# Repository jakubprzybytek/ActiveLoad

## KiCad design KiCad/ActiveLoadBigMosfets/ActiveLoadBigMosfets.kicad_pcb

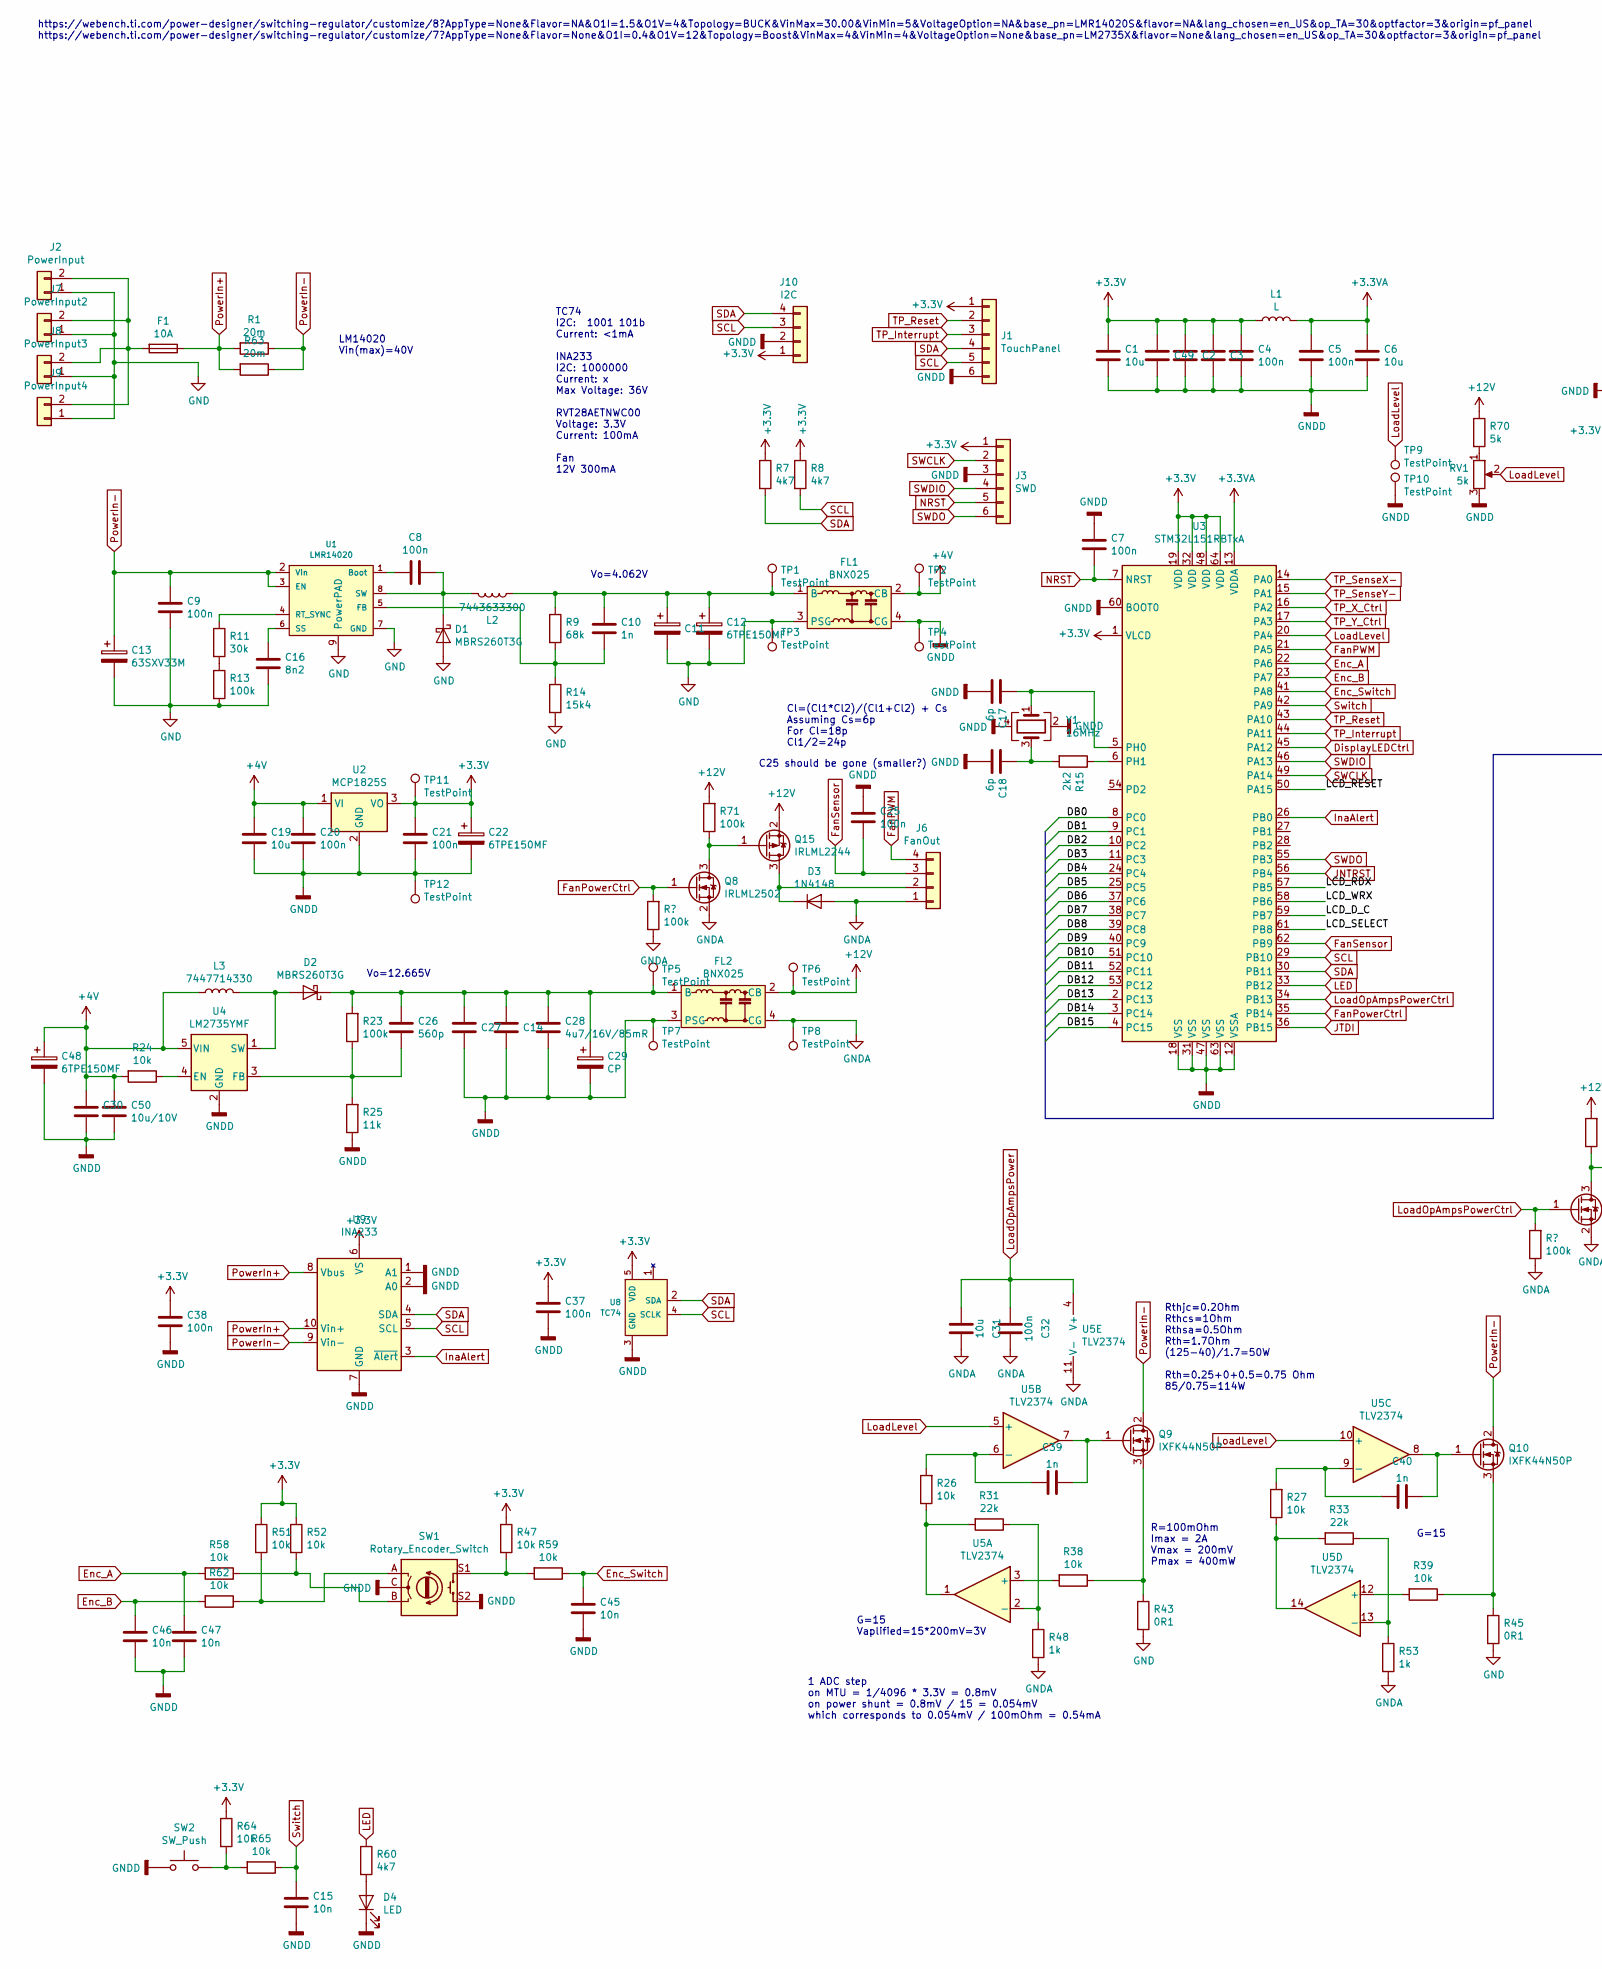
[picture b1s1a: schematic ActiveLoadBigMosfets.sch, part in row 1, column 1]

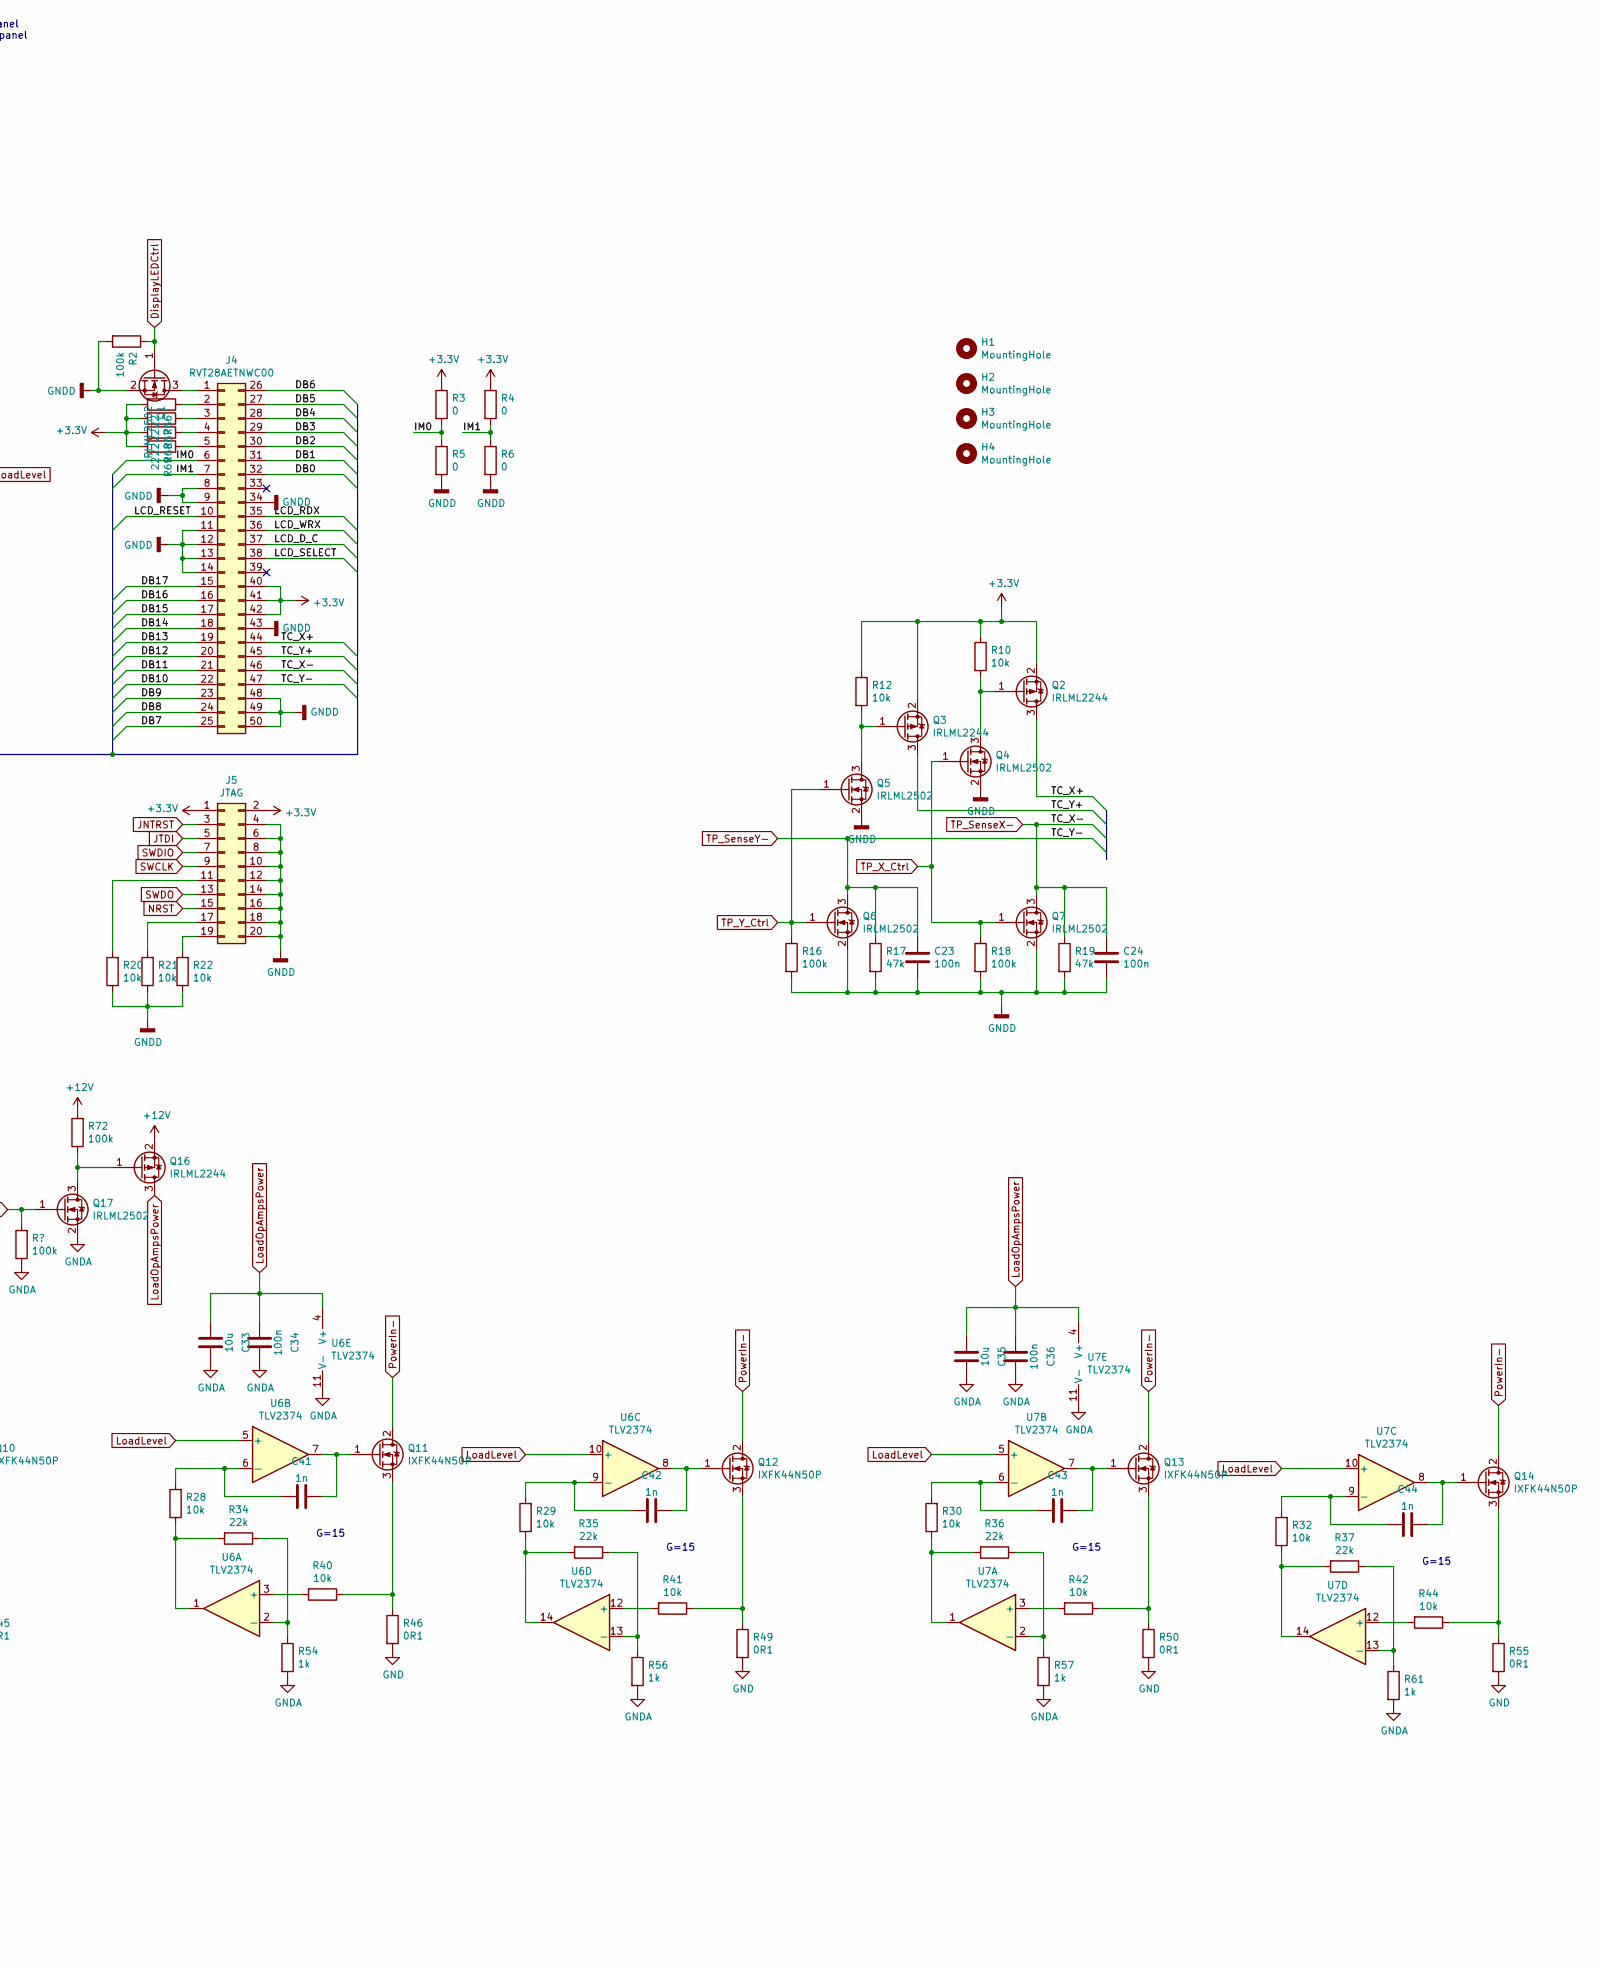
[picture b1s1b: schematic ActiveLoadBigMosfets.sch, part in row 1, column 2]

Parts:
C1, C6, C19, C31, C33, C35: 10u; C_0805_2012Metric
C2, C3, C4, C5, C7, C8, C9, C20, C21, C23, C24, C25, C32, C34, C36, C37, C38, C49: 100n; C_0603_1608Metric
C10, C39, C40, C41, C42, C43, C44: 1n; C_0805_2012Metric
C11, C12, C22, C48: 6TPE150MF; CP_EIA-7343-31_Kemet-D
C13: 63SXV33M; CP_Elec_8x11.9
C14, C27, C28: 4u7/16V/85mR; C_0805_2012Metric
C15, C45, C46, C47: 10n; C_0805_2012Metric
C16: 8n2; C_0805_2012Metric
C17, C18: 6p; C_0805_2012Metric
C26: 560p; C_0805_2012Metric
C29: CP; CP_Elec_6.3x7.7
C30, C50: 10u/10V; C_0805_2012Metric
D1, D2: MBRS260T3G; D_SMB
D3: 1N4148; D_MiniMELF
D4: LED; LED_0805_2012Metric
F1: 10A; Fuseholder5x20_horiz_open_inline_Type-I
FL1, FL2: BNX025; Filter_Murata_BNX025
H1, H2, H3, H4: MountingHole; MountingHole_3.2mm_M3
J1: TouchPanel; TE_0-1734839-6_1x06-1MP_P0.5mm_Horizontal
J2: PowerInput; SolderingHoles-2_P6.00mm_D2.0mm
J3: SWD; PinHeader_1x06_P2.54mm_Vertical
J4: RVT28AETNWC00; Molex-50S-0.5SH_1x50-P0.50mm_Horizontal
J5: JTAG; PinHeader_2x10_P2.54mm_Vertical_SMD
J6: FanOut; FanPinHeader_1x04_P2.54mm_Vertical
J7: PowerInput2; SolderingHoles-2_P6.00mm_D2.0mm
J8: PowerInput3; SolderingHoles-2_P6.00mm_D2.0mm
J9: PowerInput4; SolderingHoles-2_P6.00mm_D2.0mm
J10: I2C; PinHeader_1x04_P2.54mm_Vertical
L1: L; L_0805_2012Metric
L2: 7443633300; L_Wuerth_WE-HCF
L3: 7447714330; L_Wuerth_WE-PDF_Handsoldering
Q1, Q4, Q5, Q6, Q7, Q8, Q17: IRLML2502; SOT-23
Q2, Q3, Q15, Q16: IRLML2244; SOT-23
Q9, Q10, Q11, Q12, Q13, Q14: IXFK44N50P; TO-264-3_Vertical
R1, R63: 20m; R_2512_6332Metric_Pad1.52x3.35mm_HandSolder
R2, R13, R16, R18, R23, R71, R72: 100k; R_0805_2012Metric
R3, R6: 0; SolderJumper-2_P1.3mm_Bridged_RoundedPad1.0x1.5mm
R4, R5: 0; SolderJumper-2_P1.3mm_Open_RoundedPad1.0x1.5mm
R7, R8, R60: 4k7; R_0805_2012Metric
R9: 68k; R_0805_2012Metric
R10, R12, R20, R21, R22, R24, R26, R27, R28, R29, R30, R32, R38, R39, R40, R41, R42, R44, R47, R51, R52, R58, R59, R62, R64, R65: 10k; R_0603_1608Metric
R11: 30k; R_0805_2012Metric
R14: 15k4; R_0805_2012Metric
R15: 2k2; R_0805_2012Metric
R17, R19: 47k; R_0805_2012Metric
R25: 11k; R_0805_2012Metric
R31, R33, R34, R35, R36, R37: 22k; R_0805_2012Metric
R43, R45, R46, R49, R50, R55: 0R1; R_2512_6332Metric_Pad1.52x3.35mm_HandSolder
R48, R53, R54, R56, R57, R61: 1k; R_0805_2012Metric
R66, R67, R68, R69: 22; R_0805_2012Metric
R70: 5k; R_0805_2012Metric
RV1: 5k; Potentiometer_ACP_CA6-VSMD_Vertical
SW1: Rotary_Encoder_Switch; RotaryEncoder_Alps_EC11E-Switch_Vertical_H20mm_CircularMoun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
SW2: SW_Push; SW_SPST_B3S-1000
TP1, TP2, TP3, TP4, TP5, TP6, TP7, TP8, TP9, TP10, TP11, TP12: TestPoint; TestPoint_THTPad_1.5x1.5mm_Drill0.7mm
U1: LMR14020; SOIC-8-1EP_3.9x4.9mm_P1.27mm_EP2.41x3.3mm_ThermalVias
U2: MCP1825S; SOT-223-3_TabPin2
U3: STM32L151RBTxA; LQFP-64_10x10mm_P0.5mm
U4: LM2735YMF; SOT-23-5_HandSoldering
U5, U6, U7: TLV2374; SOIC-14_3.9x8.7mm_P1.27mm
U8: TC74; PinHeader_1x05_P2.54mm_Vertical
U9: INA233; VSSOP-10_3x3mm_P0.5mm
Y1: 16MHz; Crystal_SMD_Abracon_ABM3B-4Pin_5.0x3.2mm

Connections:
+3.3VA: C5.1, C6.1, L1.2, U3.13 (VDDA)
+3V3: C1.1, C2.1, C3.1, C4.1, C21.1, C22.1, C37.1, C38.1, C49.1, J1.1, J3.1, J4.40, J4.41, J4.42, J5.1, J5.2, J10.1, L1.1, Q2.2 (S), Q3.2 (S), R3.1, R4.1, R7.1, R8.1, R10.1, R12.1, R47.1, R51.1, R52.1, R64.1, R66.2, R67.2, R68.2, R69.2, TP11.1, U2.3 (VO), U3.1 (VLCD), U3.19 (VDD), U3.32 (VDD), U3.48 (VDD), U3.64 (VDD), U8.5 (VDD), U9.6 (VS)
+4V: C19.1, C20.1, C30.1, C48.1, C50.1, FL1.2 (CB), L3.1, R24.2, TP2.1, U2.1 (VI), U4.5 (VIN)
+12V: FL2.2 (CB), Q15.2 (S), Q16.2 (S), R70.1, R71.2, R72.2, TP6.1
/DB0: J4.32, U3.8 (PC0)
/DB1: J4.31, U3.9 (PC1)
/DB2: J4.30, U3.10 (PC2)
/DB3: J4.29, U3.11 (PC3)
/DB4: J4.28, U3.24 (PC4)
/DB5: J4.27, U3.25 (PC5)
/DB6: J4.26, U3.37 (PC6)
/DB7: J4.25, U3.38 (PC7)
/DB8: J4.24, U3.39 (PC8)
/DB9: J4.23, U3.40 (PC9)
/DB10: J4.22, U3.51 (PC10)
/DB11: J4.21, U3.52 (PC11)
/DB12: J4.20, U3.53 (PC12)
/DB13: J4.19, U3.2 (PC13)
/DB14: J4.18, U3.3 (PC14)
/DB15: J4.17, U3.4 (PC15)
/DB16: J4.16
/DB17: J4.15
/IM0: J4.6, R3.2, R5.1
/IM1: J4.7, R4.2, R6.1
/LCD_D_C: J4.37, U3.59 (PB7)
/LCD_RDX: J4.35, U3.57 (PB5)
/LCD_RESET: J4.10, U3.50 (PA15)
/LCD_SELECT: J4.38, U3.61 (PB8)
/LCD_WRX: J4.36, U3.58 (PB6)
/TC_X+: J4.44, Q2.3 (D)
/TC_Y+: J4.45, Q3.3 (D)
DisplayLEDCtrl: Q1.1 (G), R2.1, U3.45 (PA12)
Enc_A: C47.1, R58.2, U3.22 (PA6)
Enc_B: C46.1, R62.2, U3.23 (PA7)
Enc_Switch: C45.1, R59.1, U3.41 (PA8)
FanPWM: J6.4, U3.21 (PA5)
FanPowerCtrl: Q8.1 (G), U3.35 (PB14)
FanSensor: C25.2, J6.3, U3.62 (PB9)
GND: C9.2, C11.2, C12.2, C13.2, C16.2, D1.2 (A), FL1.3 (PSG), J2.1, J7.1, J8.1, J9.1, R13.2, R14.2, R43.2, R45.2, R46.2, R49.2, R50.2, R55.2, TP3.1, U1.7 (GND), U1.9 (PowerPAD)
GNDA: C31.2, C32.2, C33.1, C34.2, C35.2, C36.2, D3.2 (A), FL2.4 (CG), J6.1, Q8.2 (S), Q17.2 (S), R48.2, R53.2, R54.2, R56.2, R57.2, R61.2, TP8.1, U5.11 (V-), U6.11 (V-), U7.11 (V-)
GNDD: C1.2, C2.2, C3.2, C4.2, C5.2, C6.2, C7.1, C14.2, C15.2, C17.2, C18.2, C19.2, C20.2, C21.2, C22.2, C23.2, C24.2, C25.1, C27.2, C28.2, C29.2, C30.2, C37.2, C38.2, C45.2, C46.2, C47.2, C48.2, C49.2, C50.2, D4.1 (K), FL1.4 (CG), FL2.3 (PSG), J1.6, J3.3, J4.8, J4.9, J4.11, J4.12, J4.13, J4.14, J4.34, J4.43, J4.48, J4.49, J4.50, J5.4, J5.6, J5.8, J5.10, J5.12, J5.14, J5.16, J5.18, J5.20, J10.2, Q1.2 (S), Q4.2 (S), Q5.2 (S), Q6.2 (S), Q7.2 (S), R2.2, R5.2, R6.2, R16.2, R17.2, R18.2, R19.2, R20.1, R21.1, R22.1, R25.1, RV1.3, SW1.C, SW1.S2, SW2.1, TP4.1, TP7.1, TP10.1, TP12.1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
InaAlert: U3.26 (PB0), U9.3 (~Alert~)
JNTRST: J5.3, U3.56 (PB4)
JTDI: J5.5, U3.36 (PB15)
LED: R60.1, U3.33 (PB12)
LoadLevel: RV1.2, TP9.1, U3.20 (PA4), U5.5 (+), U5.10 (+), U6.5 (+), U6.10 (+), U7.5 (+), U7.10 (+)
LoadOpAmpsPower: C31.1, C32.1, C33.2, C34.1, C35.1, C36.1, Q16.3 (D), U5.4 (V+), U6.4 (V+), U7.4 (V+)
LoadOpAmpsPowerCtrl: Q17.1 (G), U3.34 (PB13)
NRST: C7.2, J3.5, J5.15, U3.7 (NRST)
unnamed: C8.1, D1.1 (K), L2.2, U1.8 (SW)
unnamed: C8.2, U1.1 (Boot)
unnamed: C10.1, C11.1, C12.1, FL1.1 (B), L2.1, R9.1, TP1.1
unnamed: C10.2, R9.2, R14.1, U1.5 (FB)
unnamed: C14.1, C26.1, C27.1, C28.1, C29.1, D2.1 (K), FL2.1 (B), R23.2, TP5.1
unnamed: C16.1, U1.6 (SS)
unnamed: C17.1, U3.5 (PH0), Y1.1
unnamed: C18.1, R15.2, Y1.3
unnamed: C26.2, R23.1, R25.2, U4.3 (FB)
unnamed: C39.1, R26.2, U5.6 (-)
unnamed: C39.2, Q9.1 (G), U5.7
unnamed: C40.1, R27.2, U5.9 (-)
unnamed: C40.2, Q10.1 (G), U5.8
unnamed: C41.1, R28.2, U6.6 (-)
unnamed: C41.2, Q11.1 (G), U6.7
unnamed: C42.1, R29.2, U6.9 (-)
unnamed: C42.2, Q12.1 (G), U6.8
unnamed: C43.1, R30.2, U7.6 (-)
unnamed: C43.2, Q13.1 (G), U7.7
unnamed: C44.1, R32.2, U7.9 (-)
unnamed: C44.2, Q14.1 (G), U7.8
unnamed: D2.2 (A), L3.2, U4.1 (SW)
unnamed: D3.1 (K), J6.2, Q15.3 (D)
unnamed: D4.2 (A), R60.2
unnamed: F1.2, J2.2, J7.2, J8.2, J9.2
unnamed: J4.1, Q1.3 (D)
unnamed: J4.2, R66.1
unnamed: J4.3, R67.1
unnamed: J4.4, R68.1
unnamed: J4.5, R69.1
unnamed: J5.11, R20.2
unnamed: J5.17, R21.2
unnamed: J5.19, R22.2
unnamed: Q2.1 (G), Q4.3 (D), R10.2
unnamed: Q3.1 (G), Q5.3 (D), R12.2
unnamed: Q9.3 (S), R38.1, R43.1
unnamed: Q10.3 (S), R39.1, R45.1
unnamed: Q11.3 (S), R40.1, R46.1
unnamed: Q12.3 (S), R41.1, R49.1
unnamed: Q13.3 (S), R42.1, R50.1
unnamed: Q14.3 (S), R44.1, R55.1
unnamed: Q8.3 (D), Q15.1 (G), R71.1
unnamed: Q16.1 (G), Q17.3 (D), R72.1
unnamed: R11.1, U1.4 (RT_SYNC)
unnamed: R11.2, R13.1
unnamed: R15.1, U3.6 (PH1)
unnamed: R24.1, U4.4 (EN)
unnamed: R26.1, R31.2, U5.1
unnamed: R27.1, R33.2, U5.14
unnamed: R28.1, R34.2, U6.1
unnamed: R29.1, R35.2, U6.14
unnamed: R30.1, R36.2, U7.1
unnamed: R31.1, R48.1, U5.2 (-)
unnamed: R32.1, R37.2, U7.14
unnamed: R33.1, R53.1, U5.13 (-)
unnamed: R34.1, R54.1, U6.2 (-)
unnamed: R35.1, R56.1, U6.13 (-)
unnamed: R36.1, R57.1, U7.2 (-)
unnamed: R37.1, R61.1, U7.13 (-)
unnamed: R38.2, U5.3 (+)
unnamed: R39.2, U5.12 (+)
unnamed: R40.2, U6.3 (+)
unnamed: R41.2, U6.12 (+)
unnamed: R42.2, U7.3 (+)
unnamed: R44.2, U7.12 (+)
unnamed: R47.2, R59.2, SW1.S1
unnamed: R51.2, R62.1, SW1.A
unnamed: R52.2, R58.1, SW1.B
unnamed: R64.2, R65.2, SW2.2
unnamed: R70.2, RV1.1
PowerIn+: F1.1, R1.2, R63.2, U9.8 (Vbus), U9.10 (Vin+)
PowerIn-: C9.1, C13.1, Q9.2 (D), Q10.2 (D), Q11.2 (D), Q12.2 (D), Q13.2 (D), Q14.2 (D), R1.1, R63.1, U1.2 (Vin), U1.3 (EN), U9.9 (Vin-)
SCL: J1.5, J10.3, R8.2, U3.29 (PB10), U8.4 (SCLK), U9.5 (SCL)
SDA: J1.4, J10.4, R7.2, U3.30 (PB11), U8.2 (SDA), U9.4 (SDA)
SWCLK: J3.2, J5.9, U3.49 (PA14)
SWDIO: J3.4, J5.7, U3.46 (PA13)
SWDO: J3.6, J5.13, U3.55 (PB3)
Switch: C15.1, R65.1, U3.42 (PA9)
TP_Interrupt: J1.3, U3.44 (PA11)
TP_Reset: J1.2, U3.43 (PA10)
TP_SenseX-: C24.1, J4.46, Q7.3 (D), R19.1, U3.14 (PA0)
TP_SenseY-: C23.1, J4.47, Q6.3 (D), R17.1, U3.15 (PA1)
TP_X_Ctrl: Q4.1 (G), Q7.1 (G), R18.1, U3.16 (PA2)
TP_Y_Ctrl: Q5.1 (G), Q6.1 (G), R16.1, U3.17 (PA3)

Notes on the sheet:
LM14020 Vin(max)=40V
TC74 I2C: 1001 101b Current: <1mA INA233 I2C: 1000000 Current: x Max Voltage: 36V RVT28AETNWC00 Voltage: 3.3V Current: 100mA Fan 12V 300mA
https://webench.ti.com/power-designer/switching-regulator/customize/8?AppType=None&Flavor=NA&O1I=1.5&O1V=4&Topology=BUCK&VinMax=30.00&VinMin=5&VoltageOption=NA&base_pn=LMR14020S&flavor=NA&lang_chosen=en_US&op_TA=30&optfactor=3&origin=pf_panel https://webench.ti.com/power-designer/switching-regulato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
R=100mOhm Imax = 2A Vmax = 200mV Pmax = 400mW
Rthjc=0.2Ohm Rthcs=1Ohm Rthsa=0.5Ohm Rth=1.7Ohm (125-40)/1.7=50W Rth=0.25+0+0.5=0.75 Ohm 85/0.75=114W
G=15 Vaplified=15*200mV=3V
G=15
Vo=4.062V
Vo=12.665V
1 ADC step on MTU = 1/4096 * 3.3V = 0.8mV on power shunt = 0.8mV / 15 = 0.054mV which corresponds to 0.054mV / 100mOhm = 0.54mA
Cl=(Cl1*Cl2)/(Cl1+Cl2) + Cs Assuming Cs=6p For Cl=18p Cl1/2=24p
C25 should be gone (smaller?)

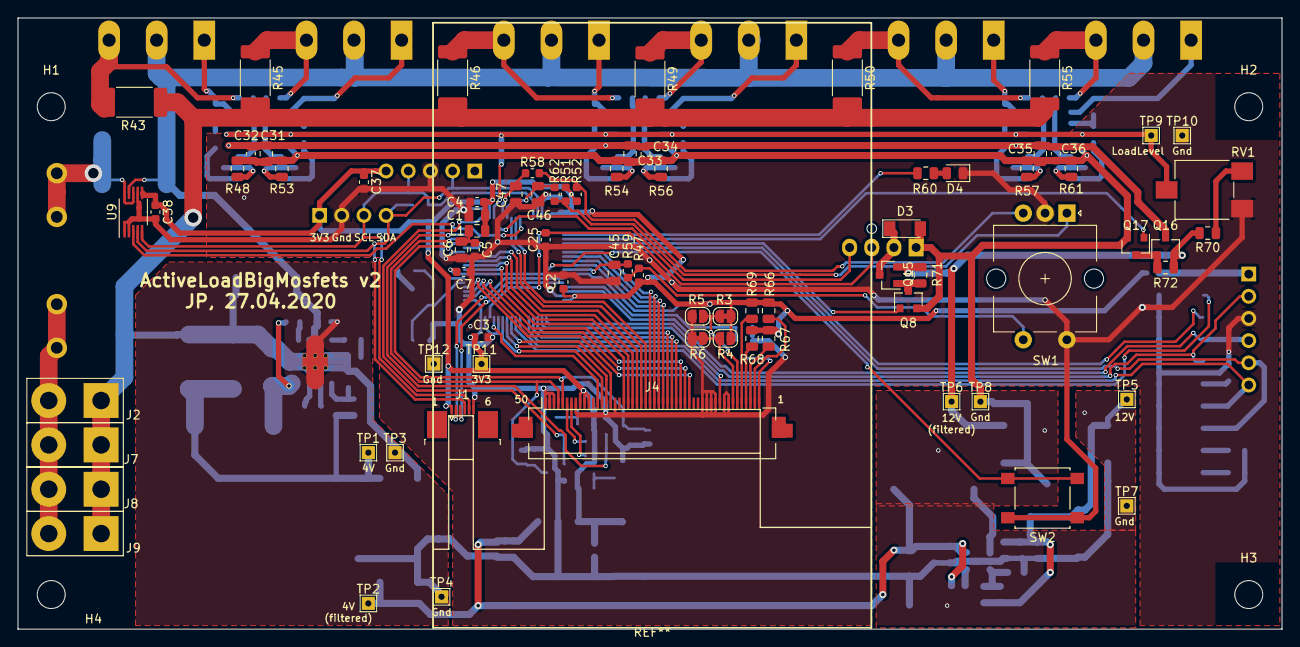
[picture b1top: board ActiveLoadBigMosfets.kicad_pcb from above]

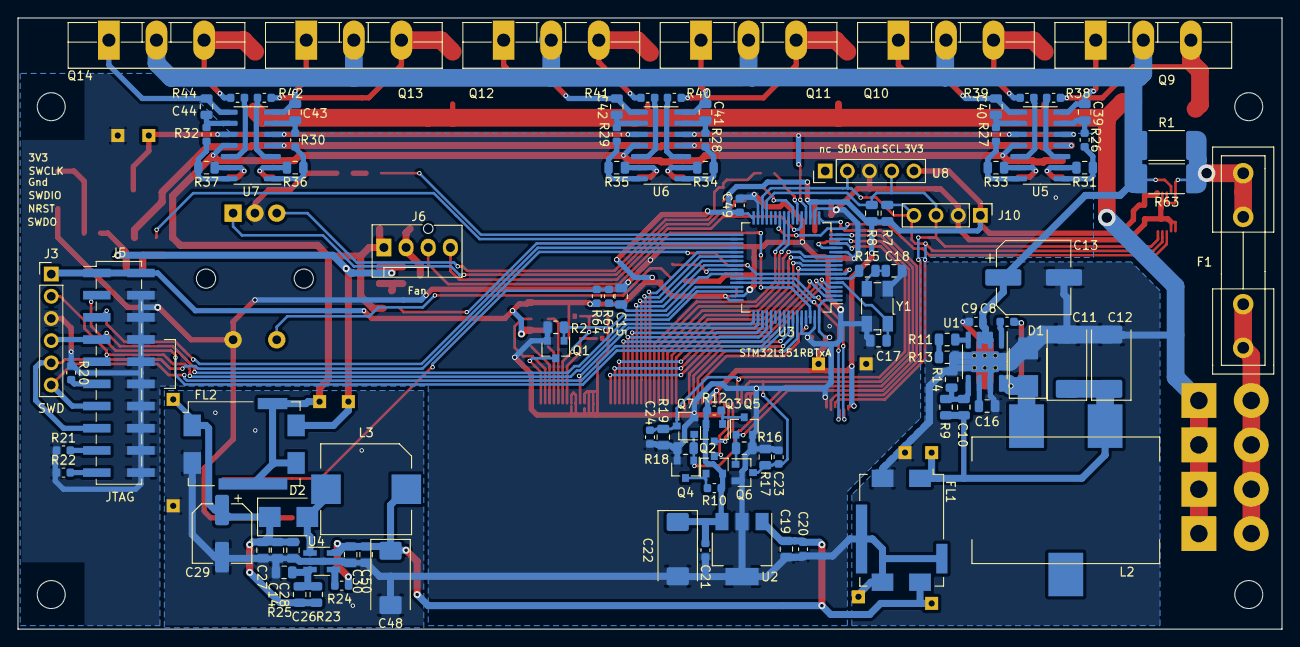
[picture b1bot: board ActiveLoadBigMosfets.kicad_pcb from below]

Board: 2 copper layers, 144.8 x 70.0 mm, 188 parts (106 on the bottom side), 131 nets.

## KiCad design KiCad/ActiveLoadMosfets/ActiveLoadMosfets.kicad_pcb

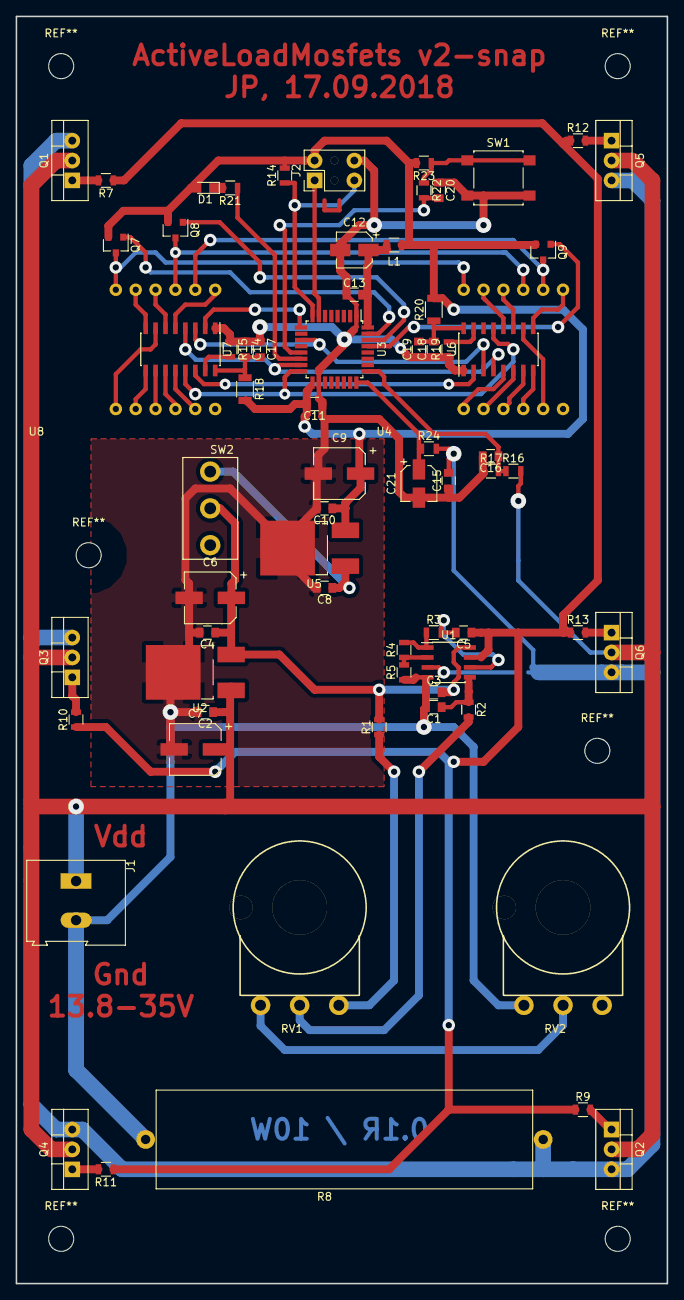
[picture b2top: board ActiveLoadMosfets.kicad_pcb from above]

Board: 2 copper layers, 83.2 x 161.9 mm, 70 parts (1 on the bottom side), 61 nets.

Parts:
C1: 220n; C_0805
C2: 470n; C_0805
C3, C4, C8, C10, C11, C13, C15, C16: 100n; C_0805
C5: 1n; C_0805
C6, C7, C9: 47u; CP_Elec_6.3x5.8
C12, C21: 10u; CP_Elec_4x5.8
C14, C19, C20: 10n; C_0805
C17, C18: 1u; C_0805
D1: LED; LED_0805
J1: Conn_01x02_Male; TerminalBlock_Altech_AK300-2_P5.00mm
J2: Conn_02x03_Odd_Even; Pin_Header_Straight_2x03_Pitch2.54mm
L1: 10u; L_0805
Q1: STP60NF06L / STP9NK60Z; TO-220-3_Vertical
Q2, Q3, Q4, Q5, Q6: STP60NF06L; TO-220-3_Vertical
Q7, Q8, Q9: IRLML2244; SOT-23
R1, R16: 47k; R_0805
R2: 5k; R_0805
R3, R14, R21, R22, R23: 10k; R_0805
R4: 6k8; R_0805
R5, R6: 1k; R_0805
R7, R9, R10, R11, R12, R13: 51; R_0805
R8: 0R1; R_Axial_Power_L48.0mm_W12.5mm_P50.8mm
R15, R19: 15k; R_0805
R17, R24: 1k1; R_0805
R18, R20: 10; R_1206
RV1: 47k; Pot_PCB-mount
RV2: 1k; Pot_PCB-mount
SW1: SW_SPST; SW_SPST_B3S-1000
SW2: SW_SPDT; SlideSwitch3Poles
U1: TLV2372; SOIC-8_3.9x4.9mm_Pitch1.27mm
U2: LM78M09; TO-252-2_Rectifier
U3: ATxmega32E5-AU; TQFP-32_7x7mm_Pitch0.8mm
U4, U8: LED-3digits; LED-14.2x3
U5: LM78M33; TO-252-2_Rectifier
U6, U7: SCT2167; SOIC-16_3.9x9.9mm_Pitch1.27mm

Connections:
+3V3: C9.1, C10.1, C11.2, D1.2, J2.2, L1.1, Q7.2, Q8.2, Q9.2, R14.2, R18.2, R20.2, R23.2, U3.17, U5.3
+12V: C3.2, C4.1, C6.1, R1.2, SW2.2, U1.8, U2.3
/+3.3Va: C12.1, C13.2, L1.2, U3.32
CURRENT: C21.1, R24.1, U3.24
Digit1: Q7.1, U3.31
Digit2: Q8.1, U3.30
Digit3: Q9.1, U3.29
GND: C1.2, C2.2, C3.1, C4.2, C6.2, C7.2, C8.2, C9.2, C10.2, C11.1, C12.2, C13.1, C14.1, C15.1, C16.2, C17.1, C18.1, C19.1, C20.1, C21.2, J1.2, J2.6, R5.1, R8.2, R15.1, R17.1, R19.1, RV2.1, SW1.2, U1.4, U2.2, U3.1, U3.18, U5.2, U6.1, U7.1
LED: R21.1, U3.14
Latch: U3.15, U6.4, U7.4
MOSI: U3.9, U7.2
unnamed: C1.1, R2.1, U1.5
unnamed: C5.1, R7.1, R9.1, R10.1, R11.1, R12.1, R13.1, U1.7
unnamed: C5.2, R3.2, U1.6
unnamed: C8.1, SW2.3, U5.1
unnamed: C14.2, C17.2, R18.1, U7.16
unnamed: C15.2, Q1.3, Q2.3, Q3.3, Q4.3, Q5.3, Q6.3, R6.1, R8.1, R24.2
unnamed: C18.2, C19.2, R20.1, U6.16
unnamed: D1.1, R21.2
unnamed: Q1.1, R7.2
unnamed: Q2.1, R9.2
unnamed: Q3.1, R10.2
unnamed: Q4.1, R11.2
unnamed: Q5.1, R12.2
unnamed: Q6.1, R13.2
unnamed: Q7.3, U4.12, U8.12
unnamed: Q8.3, U4.9, U8.9
unnamed: Q9.3, U4.8, U8.8
unnamed: R1.1, RV1.3
unnamed: R2.2, RV1.2
unnamed: R3.1, R4.2, U1.1
unnamed: R4.1, R5.2, U1.2
unnamed: R6.2, U1.3
unnamed: R15.2, U7.15
unnamed: R19.2, U6.15
unnamed: R22.1, R23.1, SW1.1
unnamed: RV1.1, RV2.2
unnamed: U4.1, U6.5
unnamed: U4.2, U6.6
unnamed: U4.3, U6.7
unnamed: U4.4, U6.8
unnamed: U4.5, U6.10
unnamed: U4.7, U6.9
unnamed: U4.10, U6.11
unnamed: U4.11, U6.12
unnamed: U6.2, U7.14
unnamed: U7.5, U8.7
unnamed: U7.6, U8.10
unnamed: U7.7, U8.1
unnamed: U7.8, U8.11
unnamed: U7.9, U8.2
unnamed: U7.10, U8.3
unnamed: U7.11, U8.4
unnamed: U7.12, U8.5
OutputEnabled: U3.16, U6.13, U7.13
PDI_CLK: J2.5, R14.1, U3.8
PDI_DATA: J2.1, U3.7
SCK: U3.11, U6.3, U7.3
SWITCH: C20.2, R22.2, U3.13
VDD: C2.1, C7.1, J1.1, Q1.2, Q2.2, Q3.2, Q4.2, Q5.2, Q6.2, R16.2, U2.1
VOLTAGE: C16.1, R16.1, R17.2, U3.25

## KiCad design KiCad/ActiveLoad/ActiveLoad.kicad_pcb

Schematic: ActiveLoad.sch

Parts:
C2, C5, C8, C10, C15, C17: 100n; C_0805
C3: 47u; CP_Elec_6.3x5.8
C4, C9: 100u; CP_Elec_6.3x7.7
C6, C11: 10u; CP_Elec_3x5.3
C7, C12, C13: 10n; C_0805
C14, C16: 1u; C_0805
C18: 200u; CP_Elec_6.3x7.7
D1, D2: 1N4148; SMD-1206_Pol
D3: BYS10-45; D_SMA
D4: LED; D_0805
J1: AuxPower; PowerSocketSMD
J2: OLED I2C; OLED_0.96inch_128x64_I2C
J3: PDI; Pin_Header_Angled_2x03_Pitch2.54mm
J4: TC74X-3.3; TO-220-5_Vertical
J5: PowerInput; PowerSocketSMD
J6: FAN; Pin_Header_Angled_1x03_Pitch2.54mm
L1: 10u; R_0805
Q2: BC817; SOT-23
Q3: BD911; TO-220-3_Vertical
Q4: BD140; TO-126_Vertical
R1, R2, R16: 2k2; R_0805
R3, R4, R5, R6, R7, R8, R9, R10, R12, R19: 10k; R_0805
R11, R15: 15k42; R_0805
R13, R25: 3k3; R_0805
R14, R17, R18, R23, R26: 1k; R_0805
R20: 0R1; R_Axial_Power_L48.0mm_W12.5mm_P50.8mm
R21: 680; R_0805
R22: 120k; R_0805
R24: 100k; R_0805
ROT1: ROTARY-ENCODER; SF-ROTARY-ENCODER
SW1, SW2: SW_SPDT; SlideSwitch3Poles
U1: UA78M33; TO-252-2_Rectifier
U2: L78M12; TO-252-2_Rectifier
U3: ATXMEGA32E5-AU; TQFP-32_7x7mm_Pitch0.8mm
U4: OPA2170; SOIC-8_3.9x4.9mm_Pitch1.27mm
U5: LM7321; SOIC-8_3.9x4.9mm_Pitch1.27mm

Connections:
+3V3: C2.1, C3.1, C5.2, C6.1, D4.2, J2.1, J3.2, J4.5, L1.1, R1.2, R2.2, R4.2, R6.2, R7.2, R8.2, U1.3 (OUT), U3.17 (VCC)
+12V: C8.1, C9.1, C15.2, C17.2, D3.1 (K), Q4.1 (E), R21.2, R26.2, SW2.1 (A), U4.8 (V+), U5.7 (V+)
CURRENT_LEVEL: Q3.3 (E), R17.1, R20.1, U3.29 (AC0OUT/AC7/ADC7/PA7)
DRAIN_CONTROL: R11.1, U3.3 (DAC1/AC3/ADC3/PA3)
ENC_A: C12.1, R9.1, U3.11 (IN2/SCK/XCK0/OC5B/OC4CHS/OC4B/PC5)
ENC_B: C13.1, R10.1, U3.12 (EXTCLK/OUT0/IN1/~SS~/OC5A/~OC4CLS~/OC4A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)
ENC_Switch: C7.2, R5.2, U3.9 (AC0OUT/IN3/MOSI/TXD0/OC4DHS/OC4D/PC7)
FAN_CONTROL: R15.1, U3.4 (DAC0/AC2/ADC2/PA2)
GND: C2.2, C3.2, C4.2, C5.1, C6.2, C7.1, C8.2, C9.2, C10.2, C11.2, C12.2, C13.2, C14.2, C15.1, C16.2, C17.1, C18.2, D1.2 (A), D2.1 (K), J1.1, J2.2, J3.6, J4.3, J5.1, J6.3, Q2.2 (E), R14.1, R18.1, R19.1, R20.2, R25.1, ROT1.3 (C), ROT1.5 (SW2), U1.2 (GND), U3.1 (GND), U3.18 (GND), U4.4 (V-), U5.4 (V-)
LED: R3.2, U3.25 (PD3/ADC11/TXD0/IN3/OC1)
unnamed: C4.1, SW1.2 (B), SW2.2 (B), U1.1 (IN)
unnamed: C10.1, C11.1, L1.2, U3.32 (AVCC)
unnamed: C14.1, R11.2, U4.6 (-)
unnamed: C16.1, R15.2, U5.2 (-)
unnamed: C18.1, D1.1 (K), J6.2, Q4.2 (C), R22.2
unnamed: D2.2 (A), U2.2 (GND)
unnamed: D3.2 (A), U2.3 (OUT)
unnamed: D4.1, R3.1
unnamed: J1.2, SW1.3 (C)
unnamed: Q2.1 (B), R16.1, R18.2
unnamed: Q2.3 (C), Q3.1 (B), R21.1
unnamed: Q4.3 (B), R23.2, R26.1
unnamed: R5.1, R6.1, ROT1.1 (SW1)
unnamed: R7.1, R9.2, ROT1.2 (A)
unnamed: R8.1, R10.2, ROT1.4 (B)
unnamed: R12.1, R13.1, U4.1
unnamed: R12.2, U4.5 (+)
unnamed: R13.2, R14.2, U4.2 (-)
unnamed: R16.2, U4.7
unnamed: R17.2, U4.3 (+)
unnamed: R19.2, R22.1, U5.3 (+)
unnamed: R23.1, U5.6
unnamed: SW2.3 (C), U2.1 (IN)
PDI_CLK: J3.5, R4.1, U3.8 (~RESET~/PDI_CLK)
PDI_DATA: J3.1, U3.7 (PDI_DATA)
PowerInput: J5.2, Q3.2 (C), R24.2, SW1.1 (A)
SCK: J2.3, J4.4, R2.1, U3.15 (IN2/SCL/XCK0/OC4AHS/OC4B/PC1)
SDA: J2.4, J4.2, R1.1, U3.16 (OUT0/IN1/SDA/~OC4ALS~/OC4A/PC0)
VOLTAGE_LEVEL: R24.1, R25.2, U3.30 (AC1OUT/AC6/ADC6/PA6)

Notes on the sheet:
32E5 (1.2mA) Display 0111 100 (80mW, 25mA) TC74 1001 xxx (0.3mA) Rot (1mA) LM358 (2mA) 1. NC 2. SDA 3. GND 4. SCK 5. VDD
Fan Control: 0-1V Fan Voltage: 0-12V G=1V/12V=12 R19/(R12+R22)=1/13
G=1/30 Voltage 0-30
Input Current 0-10A Current Level 0-1V
G=3
Max Voltage L78M12 - 35V UA78M33 - 25V OPA2170 - 36V LM7321 - 32V
Iq2=22mA
Collector to case

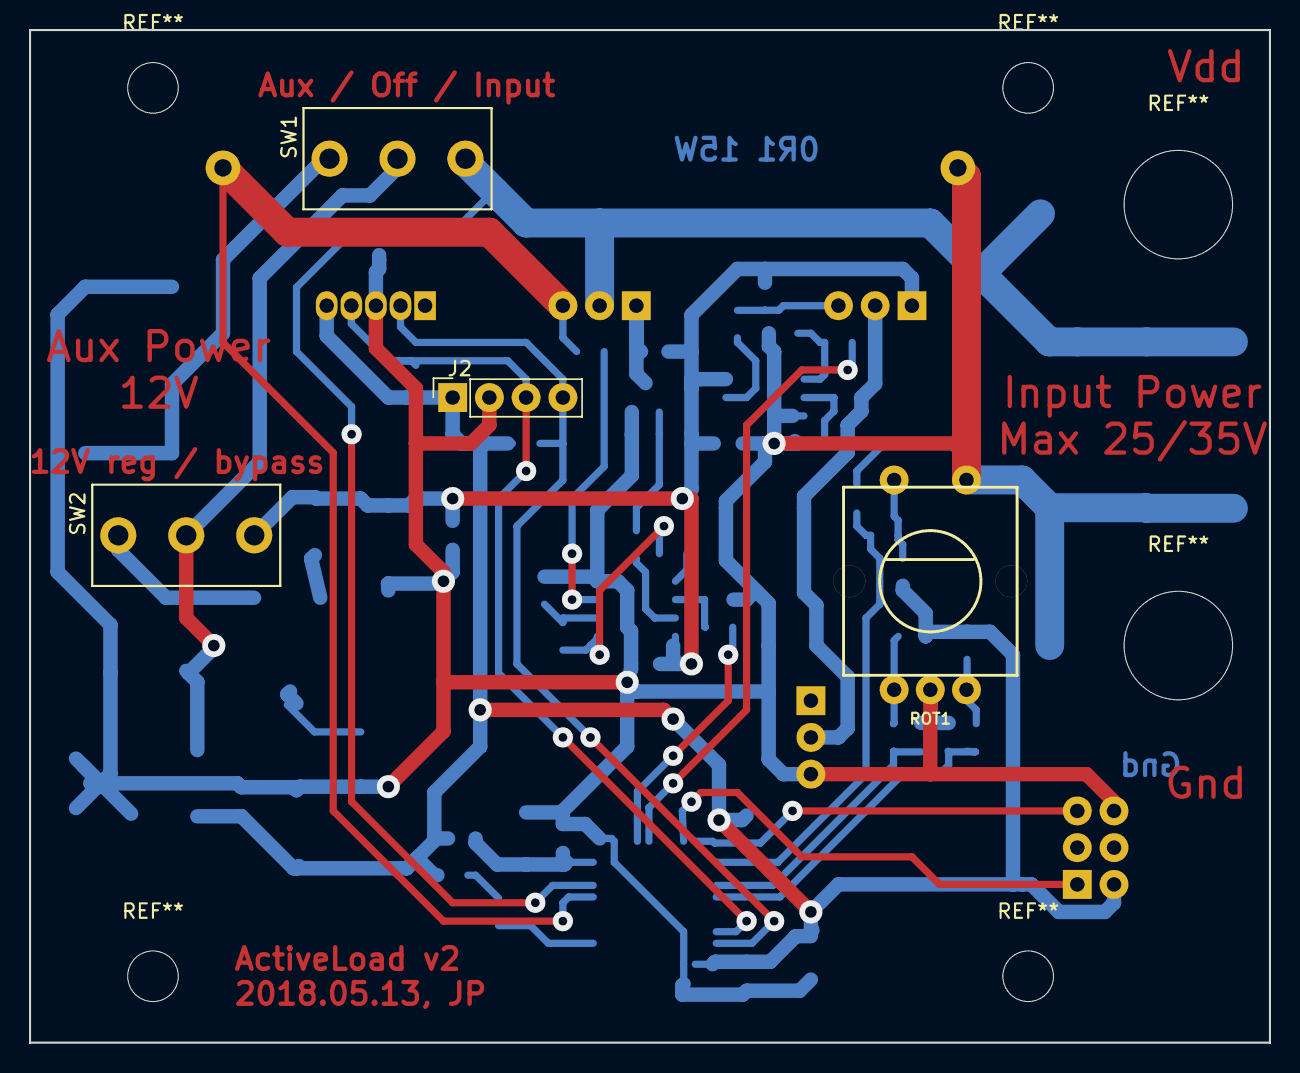
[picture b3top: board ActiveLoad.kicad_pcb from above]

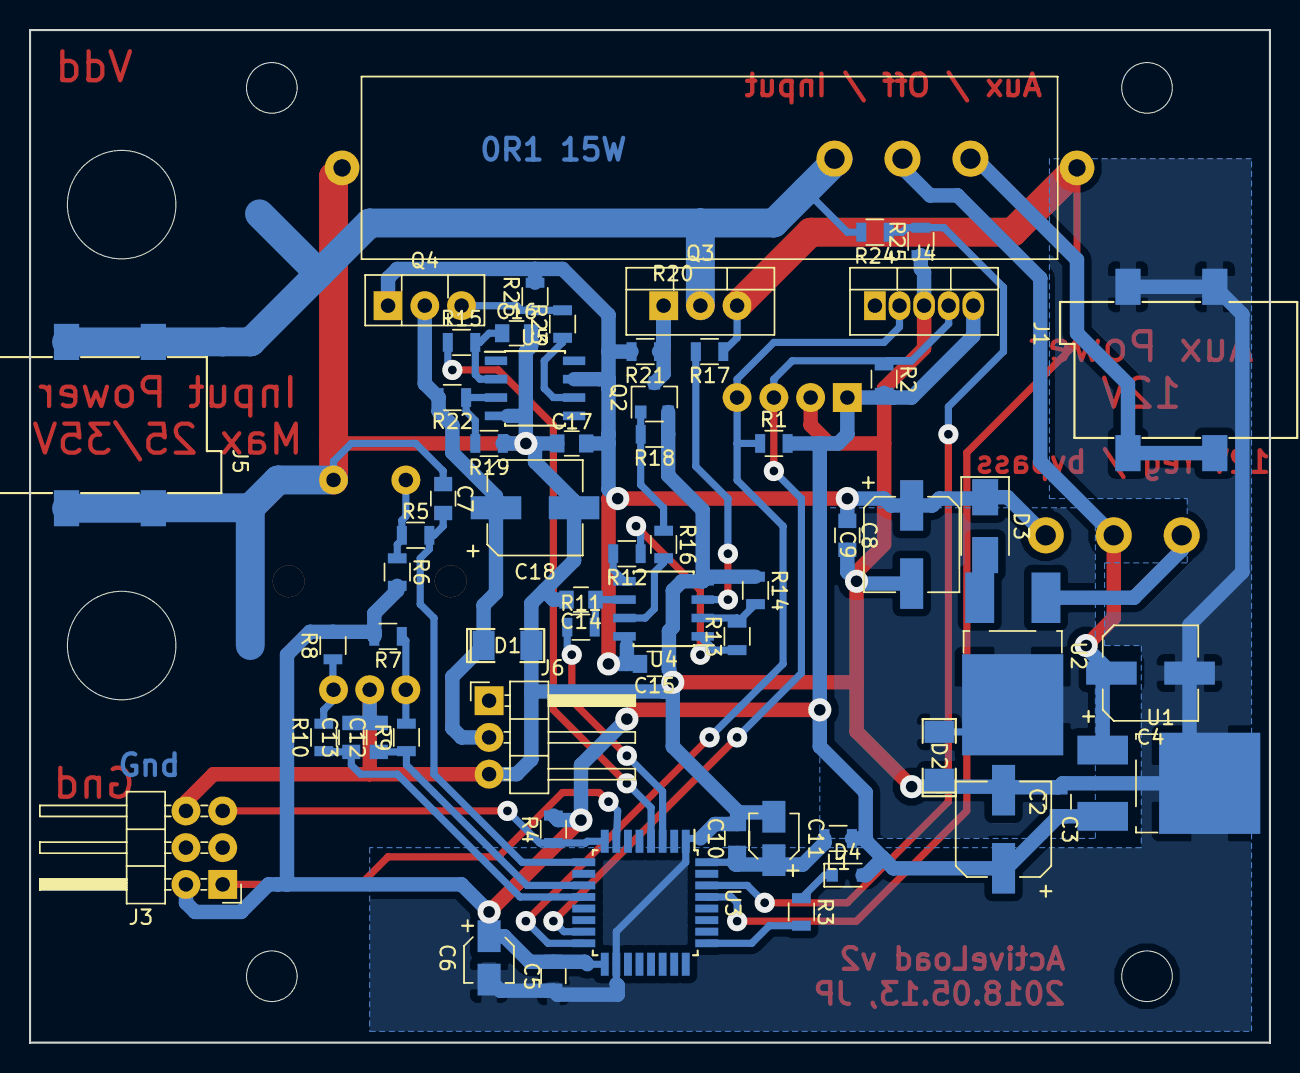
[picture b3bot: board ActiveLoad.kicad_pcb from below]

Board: 2 copper layers, 85.7 x 70.0 mm, 65 parts (61 on the bottom side), 39 nets.

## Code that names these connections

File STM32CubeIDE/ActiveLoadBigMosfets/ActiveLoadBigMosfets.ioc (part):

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Mcu.Name=STM32L151RDTx
Mcu.Package=LQFP64
Mcu.UserName=STM32L151RDTx
PA10.GPIOParameters=PinState,GPIO_Label
PA10.GPIO_Label=TouchPad Reset
PA10.PinState=GPIO_PIN_RESET
PA10.Signal=GPIO_Output
PA11.GPIOParameters=GPIO_PuPd,GPIO_Label,GPIO_ModeDefaultEXTI
PA11.GPIO_Label=TouchPad Interrupt
PA11.GPIO_ModeDefaultEXTI=GPIO_MODE_IT_RISING_FALLING
PA11.GPIO_PuPd=GPIO_PULLDOWN
PA11.Signal=GPXTI11
PA12.GPIOParameters=GPIO_PuPd,GPIO_Label
PA12.GPIO_Label=Display LED Ctrl
PA12.GPIO_PuPd=GPIO_NOPULL
PA12.Signal=GPIO_Output
PA15.GPIOParameters=GPIO_Speed,GPIO_Label
PA15.GPIO_Label=Display Reset
PA15.GPIO_Speed=GPIO_SPEED_FREQ_LOW
PA15.Signal=GPIO_Output
PA4.GPIOParameters=GPIO_Label
PA4.GPIO_Label=LoadLevel
PA4.Signal=COMP_DAC1_group
PA5.GPIOParameters=GPIO_Speed,GPIO_Label
PA5.GPIO_Label=Fan PWM
PA5.GPIO_Speed=GPIO_SPEED_FREQ_VERY_HIGH
PA5.Signal=S_TIM2_CH1_ETR
PA6.GPIOParameters=GPIO_ModeDefaultPP,GPIO_PuPd,GPIO_Label
PA6.GPIO_Label=Encoder A
PA6.GPIO_ModeDefaultPP=GPIO_MODE_AF_OD
PA6.GPIO_PuPd=GPIO_PULLUP
PA6.Signal=S_TIM3_CH1
PA7.GPIOParameters=GPIO_ModeDefaultPP,GPIO_PuPd,GPIO_Label
PA7.GPIO_Label=Encoder B
PA7.GPIO_ModeDefaultPP=GPIO_MODE_AF_OD
PA7.GPIO_PuPd=GPIO_PULLUP
PA7.Signal=S_TIM3_CH2
PA8.GPIOParameters=GPIO_PuPd,GPIO_Label,GPIO_ModeDefaultEXTI
PA8.GPIO_Label=Encoder Switch
PA8.GPIO_ModeDefaultEXTI=GPIO_MODE_IT_FALLING
PA8.GPIO_PuPd=GPIO_PULLUP
PA8.Signal=GPXTI8
PB10.Mode=I2C
PB10.Signal=I2C2_SCL
PB11.Mode=I2C
PB11.Signal=I2C2_SDA
PB12.GPIOParameters=GPIO_Label
PB12.GPIO_Label=LED
PB12.Signal=GPIO_Output
PB13.GPIOParameters=GPIO_Label
PB13.GPIO_Label=Load Op Amps Ctrl
PB13.Signal=GPIO_Output
PB14.GPIOParameters=GPIO_Label
PB14.GPIO_Label=Fan Power Ctrl
PB14.Signal=GPIO_Output
PB5.GPIOParameters=GPIO_Label
PB5.GPIO_Label=Display Read
PB5.Signal=GPIO_Output
PB6.GPIOParameters=GPIO_Speed,GPIO_Label
PB6.GPIO_Label=Display Write
PB6.GPIO_Speed=GPIO_SPEED_FREQ_HIGH
PB6.Signal=GPIO_Output
PB7.GPIOParameters=GPIO_Speed,GPIO_Label
PB7.GPIO_Label=Display Data Command
PB7.GPIO_Speed=GPIO_SPEED_FREQ_HIGH
PB7.Signal=GPIO_Output
PB8.GPIOParameters=GPIO_Label
PB8.GPIO_Label=Display Select
PB8.Signal=GPIO_Output
PB9.GPIOParameters=GPIO_PuPd,GPIO_Label,GPIO_ModeDefaultEXTI
PB9.GPIO_Label=Fan Sensor
PB9.GPIO_ModeDefaultEXTI=GPIO_MODE_IT_FALLING
PB9.GPIO_PuPd=GPIO_PULLUP
PB9.Signal=GPXTI9
PC0.GPIOParameters=GPIO_Speed
PC0.GPIO_Speed=GPIO_SPEED_FREQ_HIGH
PC0.Signal=GPIO_Output
PC1.GPIOParameters=GPIO_Speed
PC1.GPIO_Speed=GPIO_SPEED_FREQ_HIGH
PC1.Signal=GPIO_Output
PC10.GPIOParameters=GPIO_Speed
PC10.GPIO_Speed=GPIO_SPEED_FREQ_HIGH
PC10.Signal=GPIO_Output
PC11.GPIOParameters=GPIO_Speed
PC11.GPIO_Speed=GPIO_SPEED_FREQ_HIGH
PC11.Signal=GPIO_Output
PC12.GPIOParameters=GPIO_Speed
PC12.GPIO_Speed=GPIO_SPEED_FREQ_HIGH
PC12.Signal=GPIO_Output
PC13-WKUP2.GPIOParameters=GPIO_Speed
PC13-WKUP2.GPIO_Speed=GPIO_SPEED_FREQ_HIGH
PC13-WKUP2.Signal=GPIO_Output
PC14-OSC32_IN.GPIOParameters=GPIO_Speed
PC14-OSC32_IN.GPIO_Speed=GPIO_SPEED_FREQ_HIGH
PC14-OSC32_IN.Signal=GPIO_Output
PC15-OSC32_OUT.GPIOParameters=GPIO_Speed
PC15-OSC32_OUT.GPIO_Speed=GPIO_SPEED_FREQ_HIGH
PC15-OSC32_OUT.Signal=GPIO_Output
PC2.GPIOParameters=GPIO_Speed
PC2.GPIO_Speed=GPIO_SPEED_FREQ_HIGH
PC2.Signal=GPIO_Output
PC3.GPIOParameters=GPIO_Speed
PC3.GPIO_Speed=GPIO_SPEED_FREQ_HIGH
PC3.Signal=GPIO_Output
PC4.GPIOParameters=GPIO_Speed
PC4.GPIO_Speed=GPIO_SPEED_FREQ_HIGH
PC4.Signal=GPIO_Output
PC5.GPIOParameters=GPIO_Speed
PC5.GPIO_Speed=GPIO_SPEED_FREQ_HIGH
PC5.Signal=GPIO_Output
PC6.GPIOParameters=GPIO_Speed
PC6.GPIO_Speed=GPIO_SPEED_FREQ_HIGH
PC6.Signal=GPIO_Output
PC7.GPIOParameters=GPIO_Speed
PC7.GPIO_Speed=GPIO_SPEED_FREQ_HIGH
PC7.Signal=GPIO_Output
PC8.GPIOParameters=GPIO_Speed
PC8.GPIO_Speed=GPIO_SPEED_FREQ_HIGH
PC8.Signal=GPIO_Output
PC9.GPIOParameters=GPIO_Speed
PC9.GPIO_Speed=GPIO_SPEED_FREQ_HIGH
PC9.Signal=GPIO_Output
PH0-OSC_IN.Mode=HSE-External-Oscillator
PH0-OSC_IN.Signal=RCC_OSC_IN
PH1-OSC_OUT.Mode=HSE-External-Oscillator
PH1-OSC_OUT.Signal=RCC_OSC_OUT
RCC.HSE_VALUE=16000000
RCC.SYSCLKFreq_VALUE=32000000
RCC.SYSCLKSource=RCC_SYSCLKSOURCE_PLLCLK
board=custom
